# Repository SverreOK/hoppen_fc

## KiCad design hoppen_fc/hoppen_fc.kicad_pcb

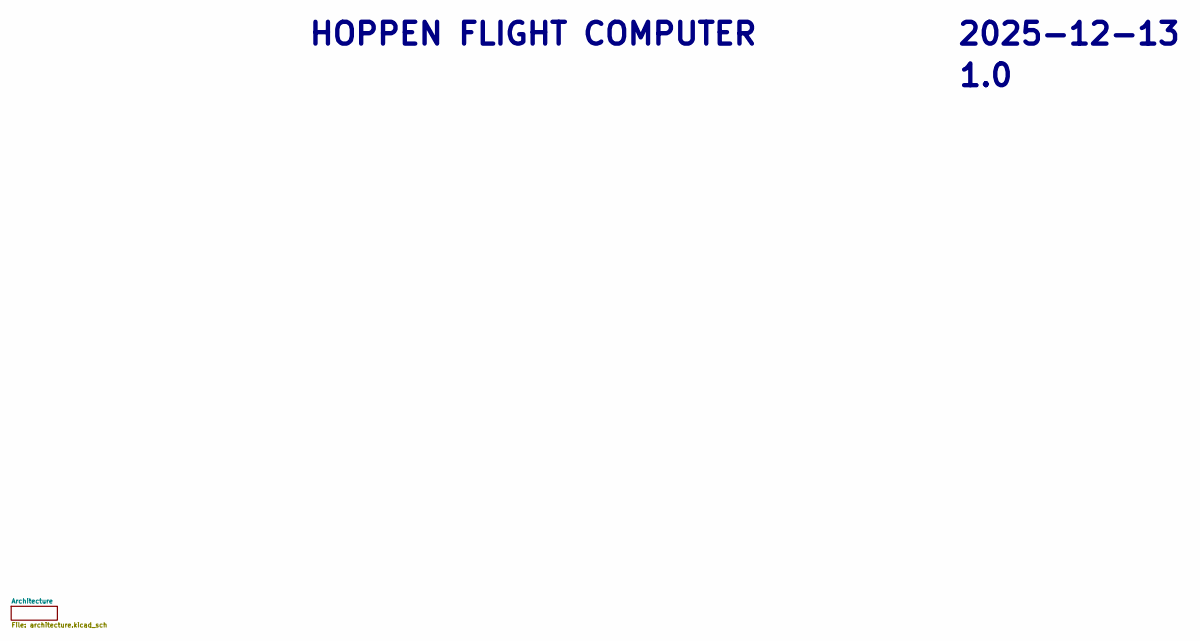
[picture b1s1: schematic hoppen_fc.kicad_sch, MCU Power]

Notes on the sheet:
${REVISION}
HOPPEN FLIGHT COMPUTER
${ISSUE_DATE}

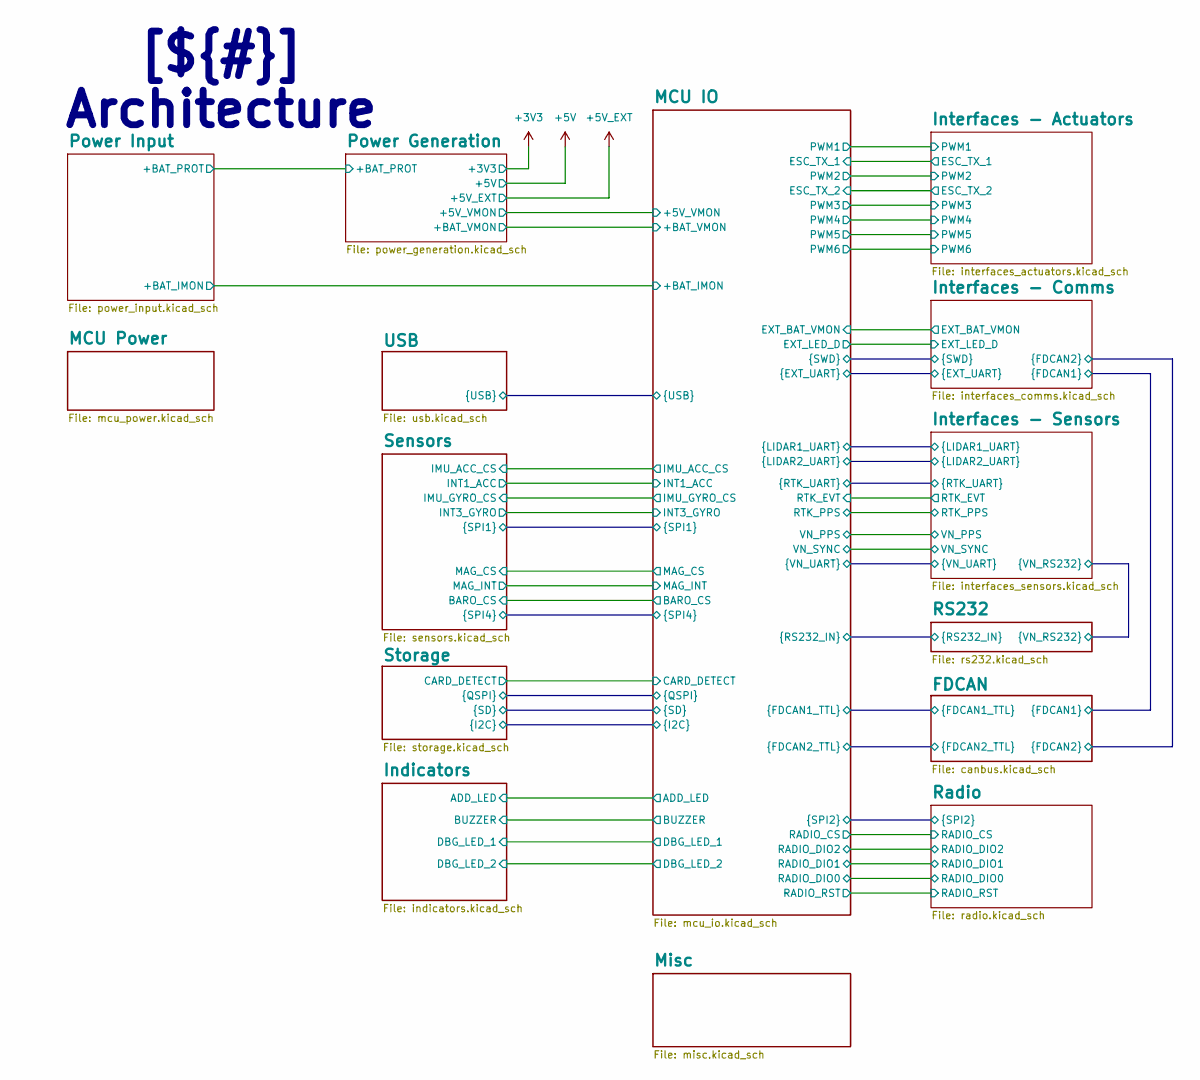
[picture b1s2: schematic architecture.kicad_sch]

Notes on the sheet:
[${#}] ${TITLE}

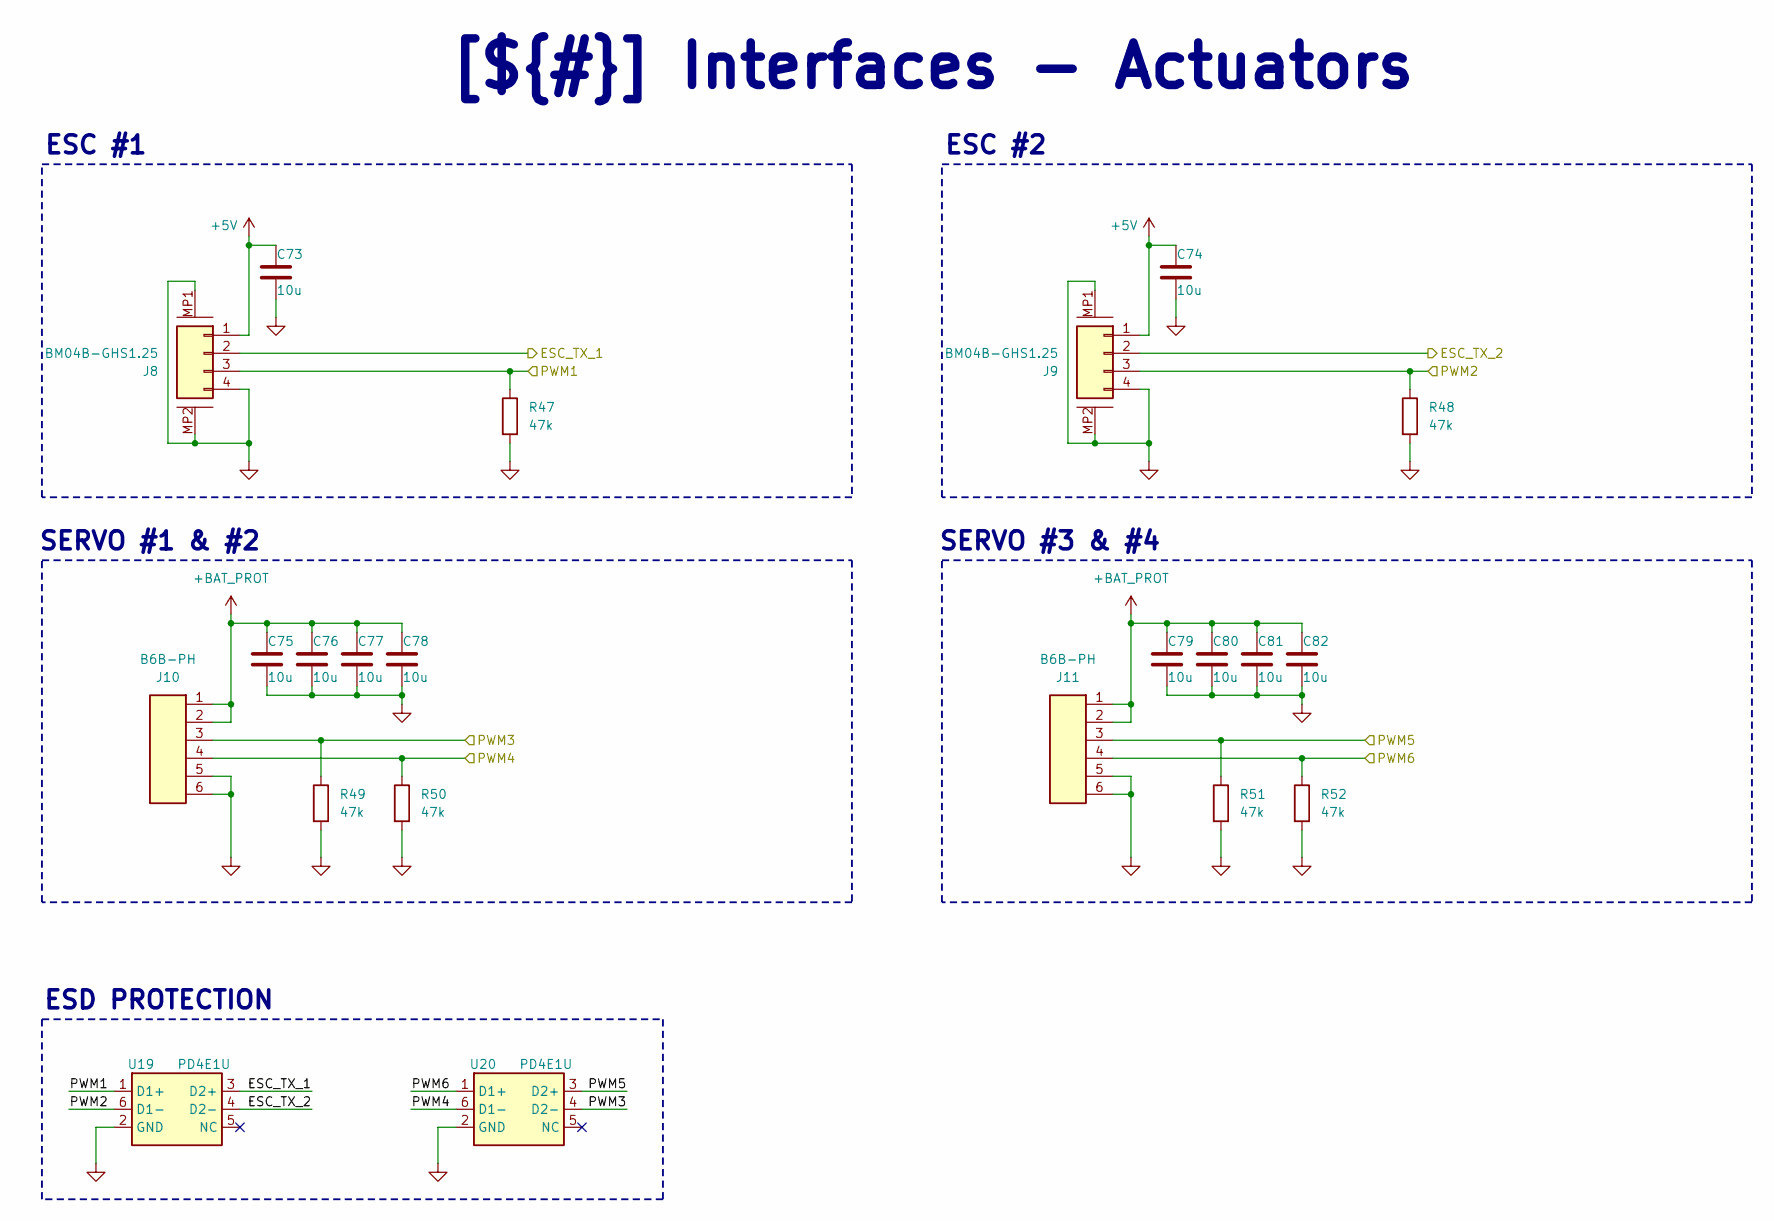
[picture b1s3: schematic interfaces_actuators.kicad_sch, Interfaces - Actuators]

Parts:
C73, C74, C75, C76, C77, C78, C79, C80, C81, C82: 10u; C_0805_2012Metric; LCSC C440198
J8, J9: BM04B-GHS1.25; LCSC C161692
J10, J11: B6B-PH; JST_PH_B6B-PH-K_1x06_P2.00mm_Vertical
R47, R48, R49, R50, R51, R52: 47k; R_0402_1005Metric; LCSC C25792
U19, U20: PD4E1U; SOT-363_SC-70-6; LCSC C194628

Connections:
+5V: C73.1, C74.1, J8.1, J9.1; also elsewhere on the board
+BAT_PROT: C75.1, C76.1, C77.1, C78.1, C79.1, C80.1, C81.1, C82.1, J10.1, J10.2, J11.1, J11.2; also elsewhere on the board
/Architecture/Interfaces - Actuators/ESC_TX_1: J8.2, U19.3 (D2+); also elsewhere on the board
/Architecture/Interfaces - Actuators/ESC_TX_2: J9.2, U19.4 (D2-); also elsewhere on the board
/Architecture/Interfaces - Actuators/PWM1: J8.3, R47.1, U19.1 (D1+); also elsewhere on the board
/Architecture/Interfaces - Actuators/PWM2: J9.3, R48.1, U19.6 (D1-); also elsewhere on the board
/Architecture/Interfaces - Actuators/PWM3: J10.3, R49.1, U20.4 (D2-); also elsewhere on the board
/Architecture/Interfaces - Actuators/PWM4: J10.4, R50.1, U20.6 (D1-); also elsewhere on the board
/Architecture/Interfaces - Actuators/PWM5: J11.3, R51.1, U20.3 (D2+); also elsewhere on the board
/Architecture/Interfaces - Actuators/PWM6: J11.4, R52.1, U20.1 (D1+); also elsewhere on the board
GND: C73.2, C74.2, C75.2, C76.2, C77.2, C78.2, C79.2, C80.2, C81.2, C82.2, J8.4, J8.MP1, J8.MP2, J9.4, J9.MP1, J9.MP2, J10.5, J10.6, J11.5, J11.6, R47.2, R48.2, R49.2, R50.2, R51.2, R52.2, U19.2 (GND), U20.2 (GND); also elsewhere on the board

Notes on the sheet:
SERVO #1 & #2
ESD PROTECTION
SERVO #3 & #4
ESC #2
ESC #1
[${#}] ${TITLE}

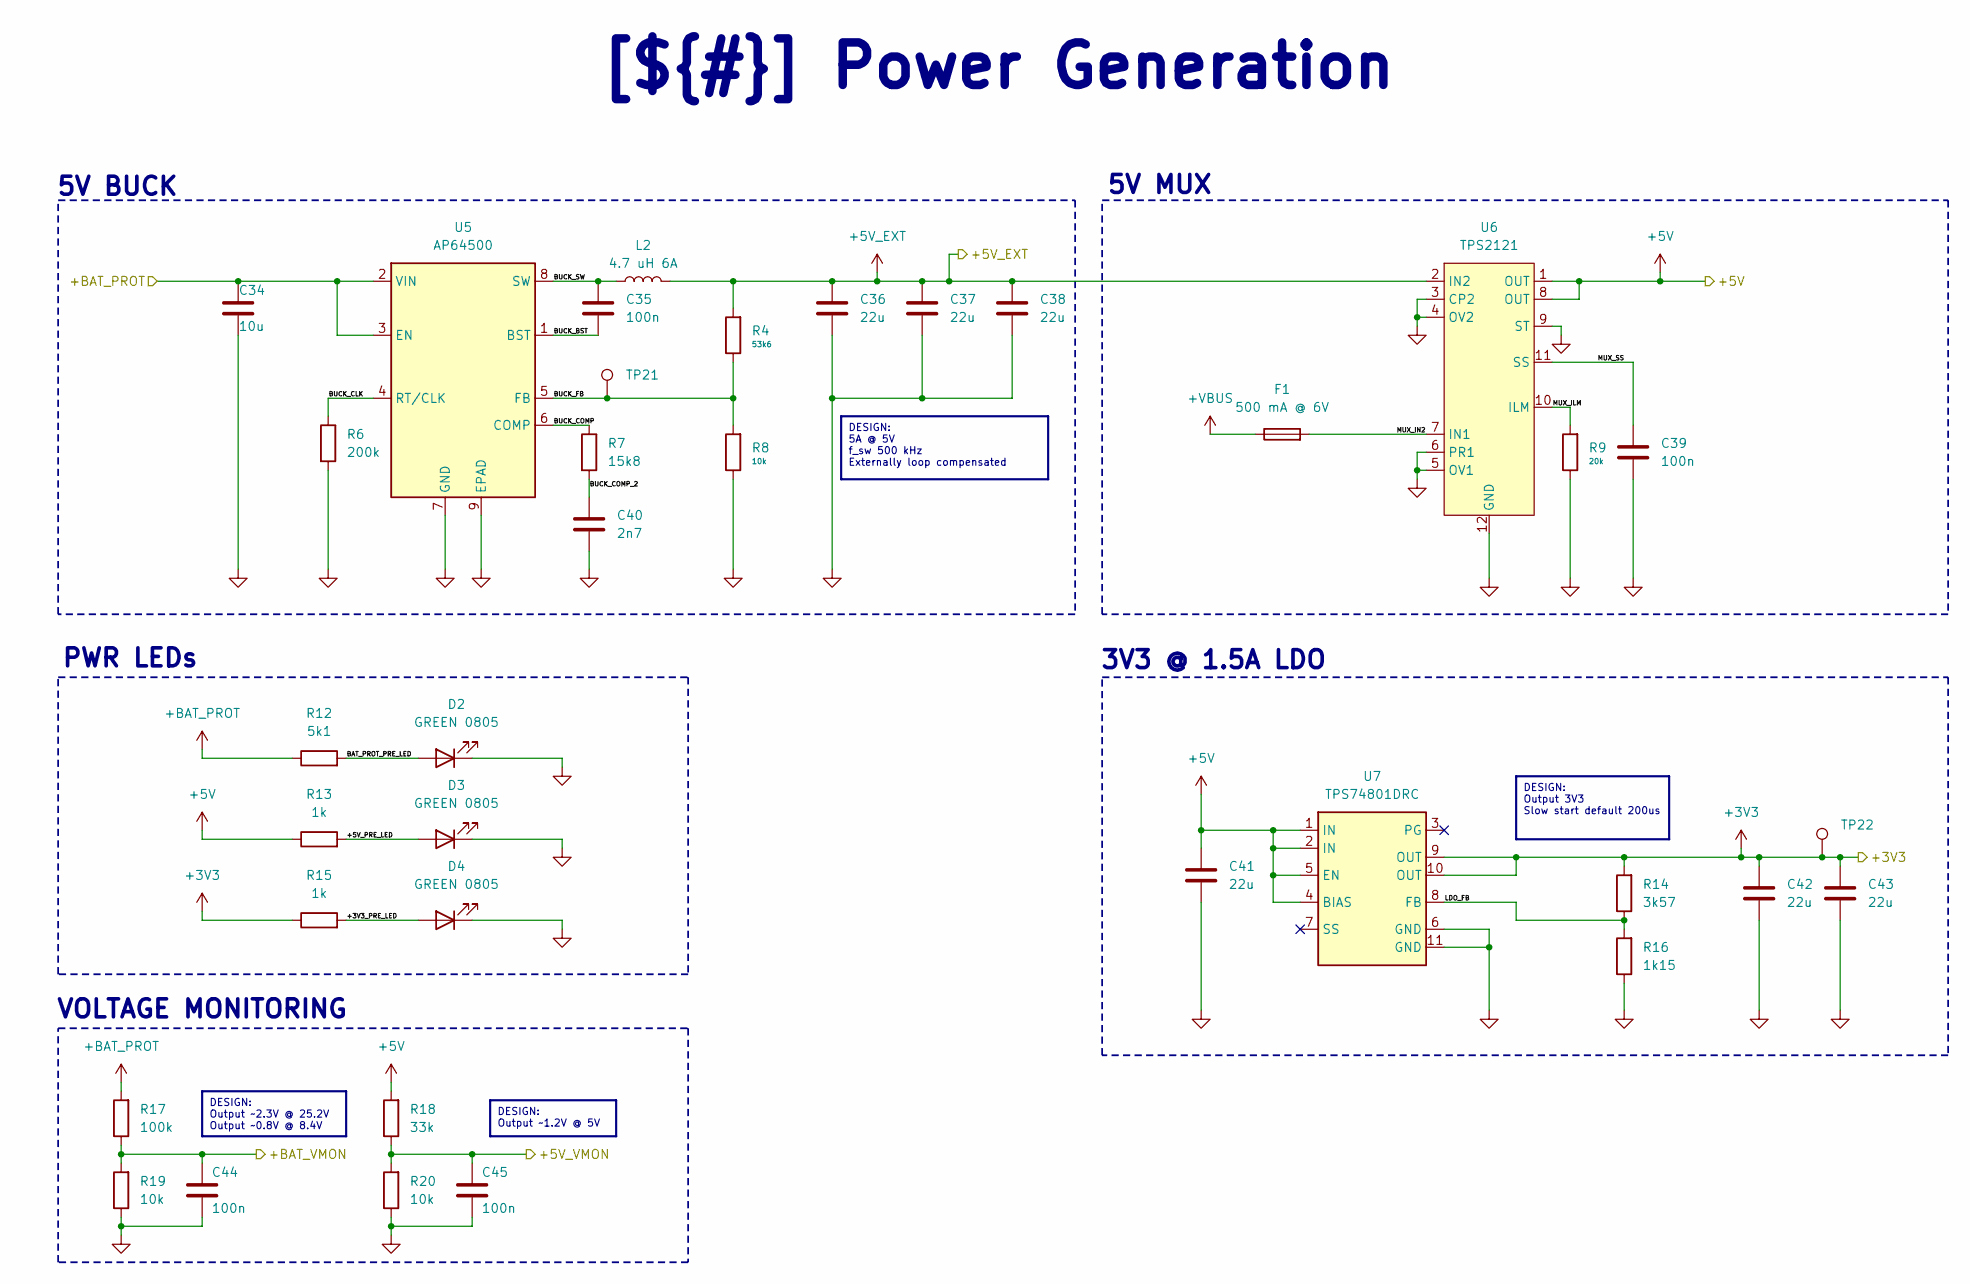
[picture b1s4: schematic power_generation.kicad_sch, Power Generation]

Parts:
C34: 10u; C_0805_2012Metric; LCSC C440198
C35, C39, C44, C45: 100n; C_0402_1005Metric; LCSC C307331
C36, C37, C38, C41, C42, C43: 22u; C_0805_2012Metric; LCSC C45783
C40: 2n7; C_0402_1005Metric; LCSC C106251
D2, D3, D4: GREEN 0805; LED_0805_2012Metric; LCSC C2297
F1: 500 mA @ 6V; Fuse_0603_1608Metric; LCSC C210357
L2: 4.7 uH 6A; IND-SMD_L7.2-W6.6_GPSR07X0; LCSC C5189754
R4: 53k6; R_0402_1005Metric; LCSC C53398
R6: 200k; R_0402_1005Metric; LCSC C25764
R7: 15k8; R_0402_1005Metric; LCSC C26956
R8, R19, R20: 10k; R_0402_1005Metric; LCSC C25744
R9: 20k; R_0402_1005Metric; LCSC C25765
R12: 5k1; R_0402_1005Metric; LCSC C25905
R13, R15: 1k; R_0402_1005Metric; LCSC C106235
R14: 3k57; R_0402_1005Metric; LCSC C270609
R16: 1k15; R_0402_1005Metric; LCSC C5159680
R17: 100k; R_0402_1005Metric; LCSC C25741
R18: 33k; R_0402_1005Metric; LCSC C25779
TP21, TP22: TestPoint; TestPoint_Pad_1.0x1.0mm
U5: AP64500; SO-8-EP; LCSC C2070920
U6: TPS2121; Texas_VQFN-HR-12_2x2.5mm_P0.5mm; LCSC C2156025
U7: TPS74801DRC; VSON-10; LCSC C105263

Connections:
+3V3: C42.1, C43.1, R14.2, R15.1, TP22.1, U7.9 (OUT), U7.10 (OUT); also elsewhere on the board
+5V: C41.1, R13.1, R18.2, U6.1 (OUT), U6.8 (OUT), U7.1 (IN), U7.2 (IN), U7.4 (BIAS), U7.5 (EN); also elsewhere on the board
+5V_EXT: C36.1, C37.1, C38.1, L2.2, R4.2, U6.2 (IN2); also elsewhere on the board
+BAT_PROT: C34.1, R12.1, R17.2, U5.2 (VIN), U5.3 (EN); also elsewhere on the board
+VBUS: F1.1; also elsewhere on the board
/Architecture/MCU IO/+5V_VMON: C45.2, R18.1, R20.2; also elsewhere on the board
/Architecture/MCU IO/+BAT_VMON: C44.2, R17.1, R19.2; also elsewhere on the board
/Architecture/Power Generation/+3V3_PRE_LED: D4.2 (A), R15.2
/Architecture/Power Generation/+5V_PRE_LED: D3.2 (A), R13.2
/Architecture/Power Generation/BAT_PROT_PRE_LED: D2.2 (A), R12.2
/Architecture/Power Generation/BUCK_BST: C35.2, U5.1 (BST)
/Architecture/Power Generation/BUCK_CLK: R6.1, U5.4 (RT/CLK)
/Architecture/Power Generation/BUCK_COMP: R7.1, U5.6 (COMP)
/Architecture/Power Generation/BUCK_COMP_2: C40.1, R7.2
/Architecture/Power Generation/BUCK_FB: R4.1, R8.2, TP21.1, U5.5 (FB)
/Architecture/Power Generation/BUCK_SW: C35.1, L2.1, U5.8 (SW)
/Architecture/Power Generation/LDO_FB: R14.1, R16.2, U7.8 (FB)
/Architecture/Power Generation/MUX_ILM: R9.2, U6.10 (ILM)
/Architecture/Power Generation/MUX_IN2: F1.2, U6.7 (IN1)
/Architecture/Power Generation/MUX_SS: C39.1, U6.11 (SS)
GND: C34.2, C36.2, C37.2, C38.2, C39.2, C40.2, C41.2, C42.2, C43.2, C44.1, C45.1, D2.1 (K), D3.1 (K), D4.1 (K), R6.2, R8.1, R9.1, R16.1, R19.1, R20.1, U5.7 (GND), U5.9 (EPAD), U6.3 (CP2), U6.4 (OV2), U6.5 (OV1), U6.6 (PR1), U6.9 (ST), U6.12 (GND), U7.6 (GND), U7.11 (GND); also elsewhere on the board

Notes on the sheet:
5V MUX
PWR LEDs
5V BUCK
VOLTAGE MONITORING
3V3 @ 1.5A LDO
[${#}] ${TITLE}
DESIGN: Output 3V3 Slow start default 200us
DESIGN: 5A @ 5V f_sw 500 kHz Externally loop compensated
DESIGN: Output ~1.2V @ 5V
DESIGN: Output ~2.3V @ 25.2V Output ~0.8V @ 8.4V

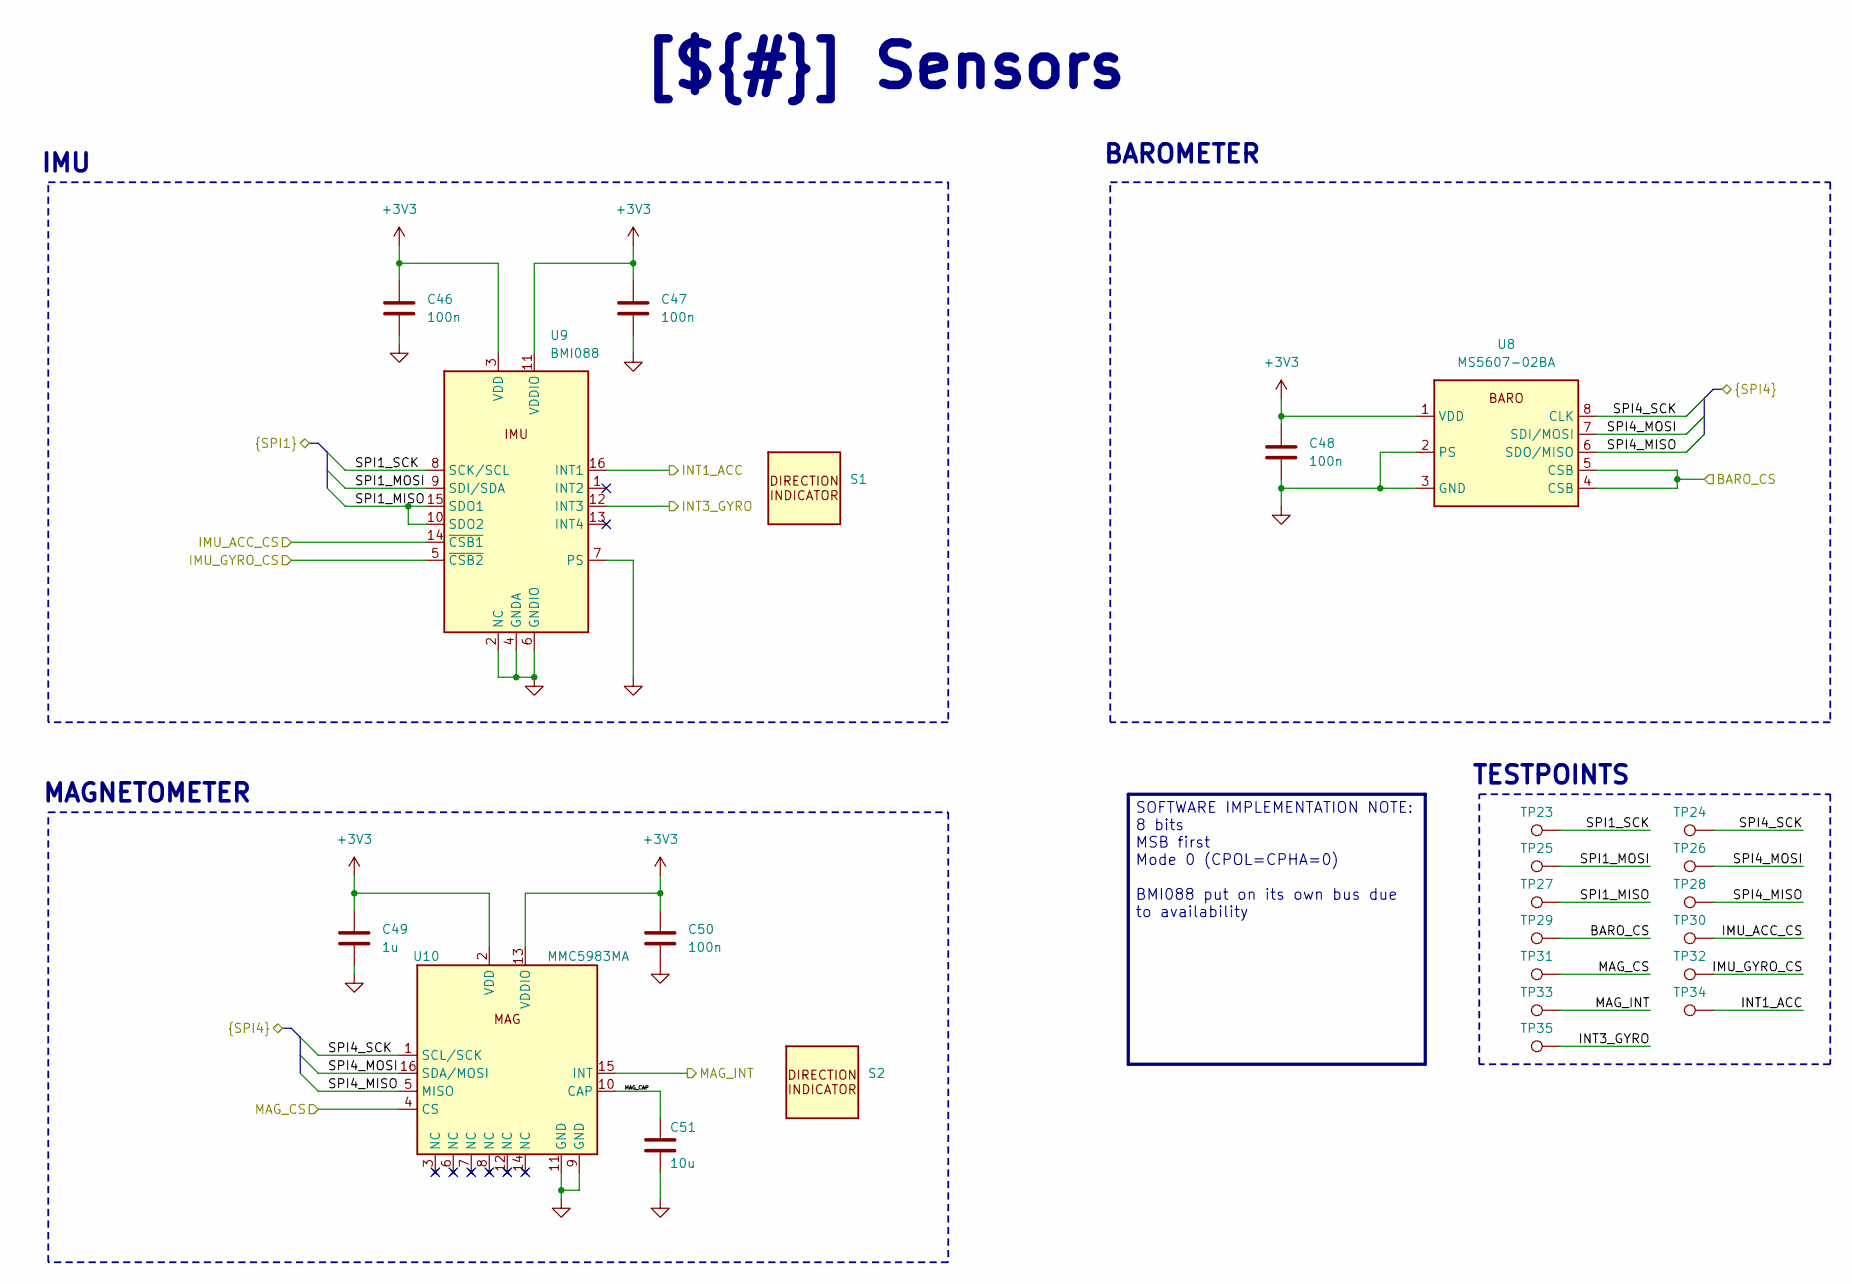
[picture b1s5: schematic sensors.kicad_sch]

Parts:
C46, C47, C48, C50: 100n; C_0402_1005Metric; LCSC C307331
C49: 1u; C_0402_1005Metric; LCSC C52923
C51: 10u; C_0805_2012Metric; LCSC C440198
S1: right_hand_rule
S2: right_hand_rule_2
TP23, TP24, TP25, TP26, TP27, TP28, TP29, TP30, TP31, TP32, TP33, TP34, TP35: TestPoint; TestPoint_Pad_1.0x1.0mm
U8: MS5607-02BA; LGA-8_3x5mm_P1.25mm; LCSC C97627
U9: BMI088; Bosch_LGA-16_4.5x3mm_P0.5mm_LayoutBorder7x1y_ClockwisePinNu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; LCSC C194919
U10: MMC5983MA; LGA-16_3x3mm_P0.5mm; LCSC C404329

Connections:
+3V3: C46.1, C47.1, C48.1, C49.1, C50.1, U8.1 (VDD), U9.3 (VDD), U9.11 (VDDIO), U10.2 (VDD), U10.13 (VDDIO); also elsewhere on the board
/Architecture/MCU IO/BARO_CS: TP29.1, U8.4 (CSB), U8.5 (CSB); also elsewhere on the board
/Architecture/MCU IO/IMU_ACC_CS: TP30.1, U9.14 (~CSB1); also elsewhere on the board
/Architecture/MCU IO/IMU_GYRO_CS: TP32.1, U9.5 (~CSB2); also elsewhere on the board
/Architecture/MCU IO/INT1_ACC: TP34.1, U9.16 (INT1); also elsewhere on the board
/Architecture/MCU IO/INT3_GYRO: TP35.1, U9.12 (INT3); also elsewhere on the board
/Architecture/MCU IO/MAG_CS: TP31.1, U10.4 (CS); also elsewhere on the board
/Architecture/MCU IO/MAG_INT: TP33.1, U10.15 (INT); also elsewhere on the board
/Architecture/MCU IO/SPI1_MISO: TP27.1, U9.10 (SDO2), U9.15 (SDO1); also elsewhere on the board
/Architecture/MCU IO/SPI1_MOSI: TP25.1, U9.9 (SDI/SDA); also elsewhere on the board
/Architecture/MCU IO/SPI1_SCK: TP23.1, U9.8 (SCK/SCL); also elsewhere on the board
/Architecture/MCU IO/SPI4_MISO: TP28.1, U8.6 (SDO/MISO), U10.5 (MISO); also elsewhere on the board
/Architecture/MCU IO/SPI4_MOSI: TP26.1, U8.7 (SDI/MOSI), U10.16 (SDA/MOSI); also elsewhere on the board
/Architecture/MCU IO/SPI4_SCK: TP24.1, U8.8 (CLK), U10.1 (SCL/SCK); also elsewhere on the board
/Architecture/Sensors/MAG_CAP: C51.2, U10.10 (CAP)
GND: C46.2, C47.2, C48.2, C49.2, C50.2, C51.1, U8.2 (PS), U8.3 (GND), U9.2 (NC), U9.4 (GNDA), U9.6 (GNDIO), U9.7 (PS), U10.9 (GND), U10.11 (GND); also elsewhere on the board

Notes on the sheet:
BAROMETER
MAGNETOMETER
TESTPOINTS
IMU
[${#}] ${TITLE}
SOFTWARE IMPLEMENTATION NOTE: 8 bits MSB first Mode 0 (CPOL=CPHA=0) BMI088 put on its own bus due to availability

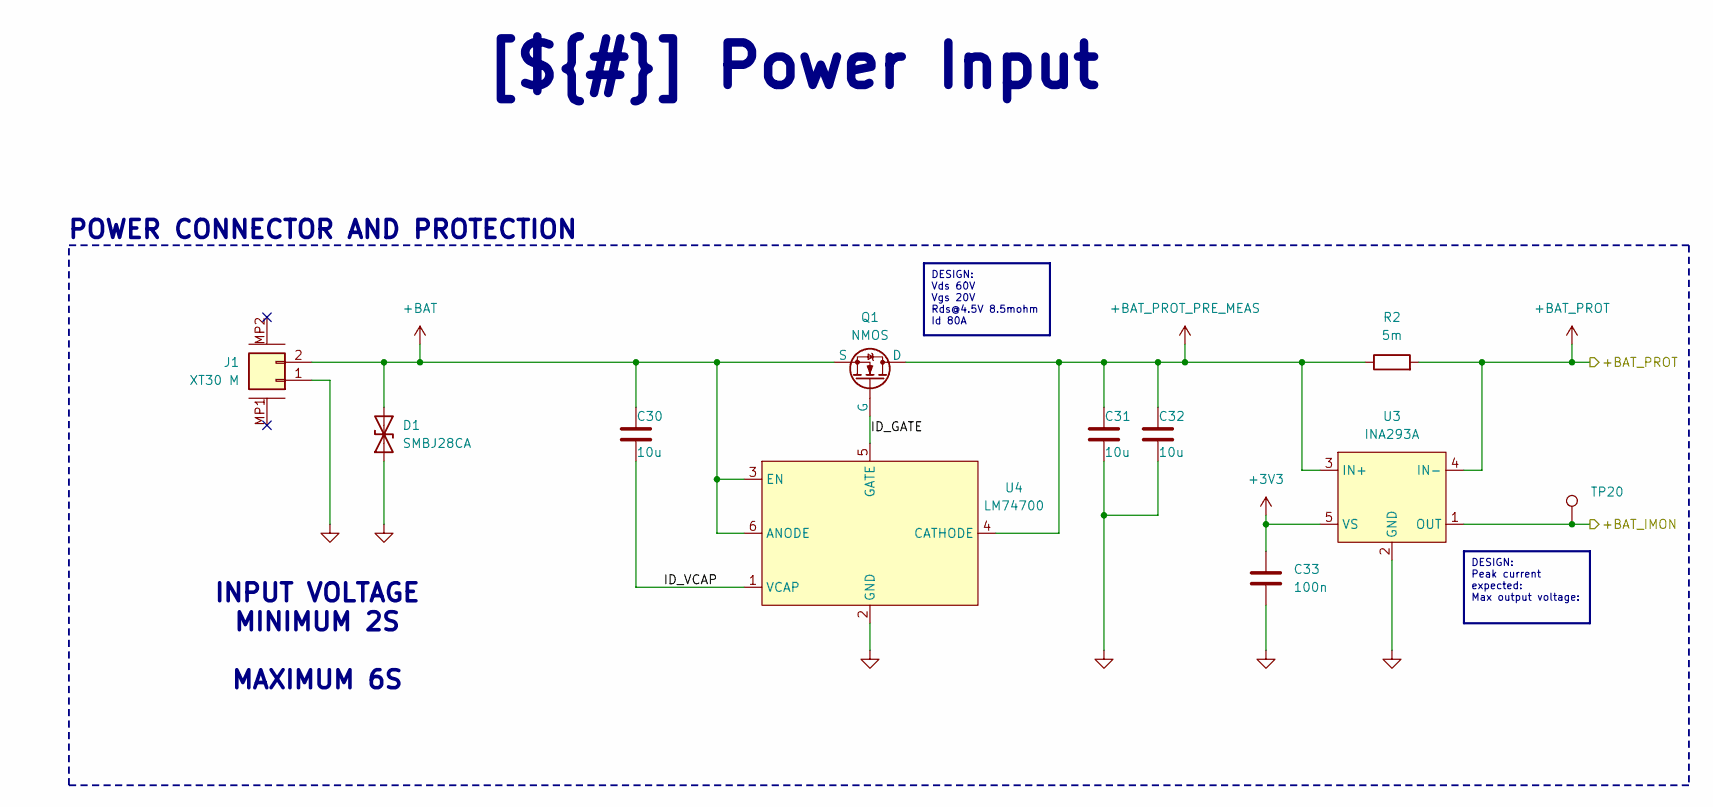
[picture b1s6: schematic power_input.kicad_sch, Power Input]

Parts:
C30, C31, C32: 10u; C_0805_2012Metric; LCSC C440198
C33: 100n; C_0402_1005Metric; LCSC C307331
D1: SMBJ28CA; D_SMB; LCSC C19077583
J1: XT30 M; XT30PW-M
Q1: NMOS; Diodes_PowerDI3333-8; LCSC C2802568
R2: 5m; R_2512_6332Metric; LCSC C185817
TP20: TestPoint; TestPoint_Pad_1.0x1.0mm
U3: INA293A; SOT-23-5; LCSC C1855790
U4: LM74700; SOT-23-6; LCSC C2941042

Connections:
+3V3: C33.1, U3.5 (VS); also elsewhere on the board
+BAT: C30.1, D1.2 (A2), J1.2, Q1.3 (S), U4.3 (EN), U4.6 (ANODE)
+BAT_PROT: R2.2, U3.4 (IN-); also elsewhere on the board
+BAT_PROT_PRE_MEAS: C31.1, C32.1, Q1.1 (D), R2.1, U3.3 (IN+), U4.4 (CATHODE)
/Architecture/MCU IO/+BAT_IMON: TP20.1, U3.1 (OUT); also elsewhere on the board
/Architecture/Power Input/ID_GATE: Q1.2 (G), U4.5 (GATE)
/Architecture/Power Input/ID_VCAP: C30.2, U4.1 (VCAP)
GND: C31.2, C32.2, C33.2, D1.1 (A1), J1.1, U3.2 (GND), U4.2 (GND); also elsewhere on the board

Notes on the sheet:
POWER CONNECTOR AND PROTECTION
INPUT VOLTAGE MINIMUM 2S MAXIMUM 6S
DESIGN: Peak current expected: Max output voltage:
[${#}] ${TITLE}
DESIGN: Vds 60V Vgs 20V Rds@4.5V 8.5mohm Id 80A

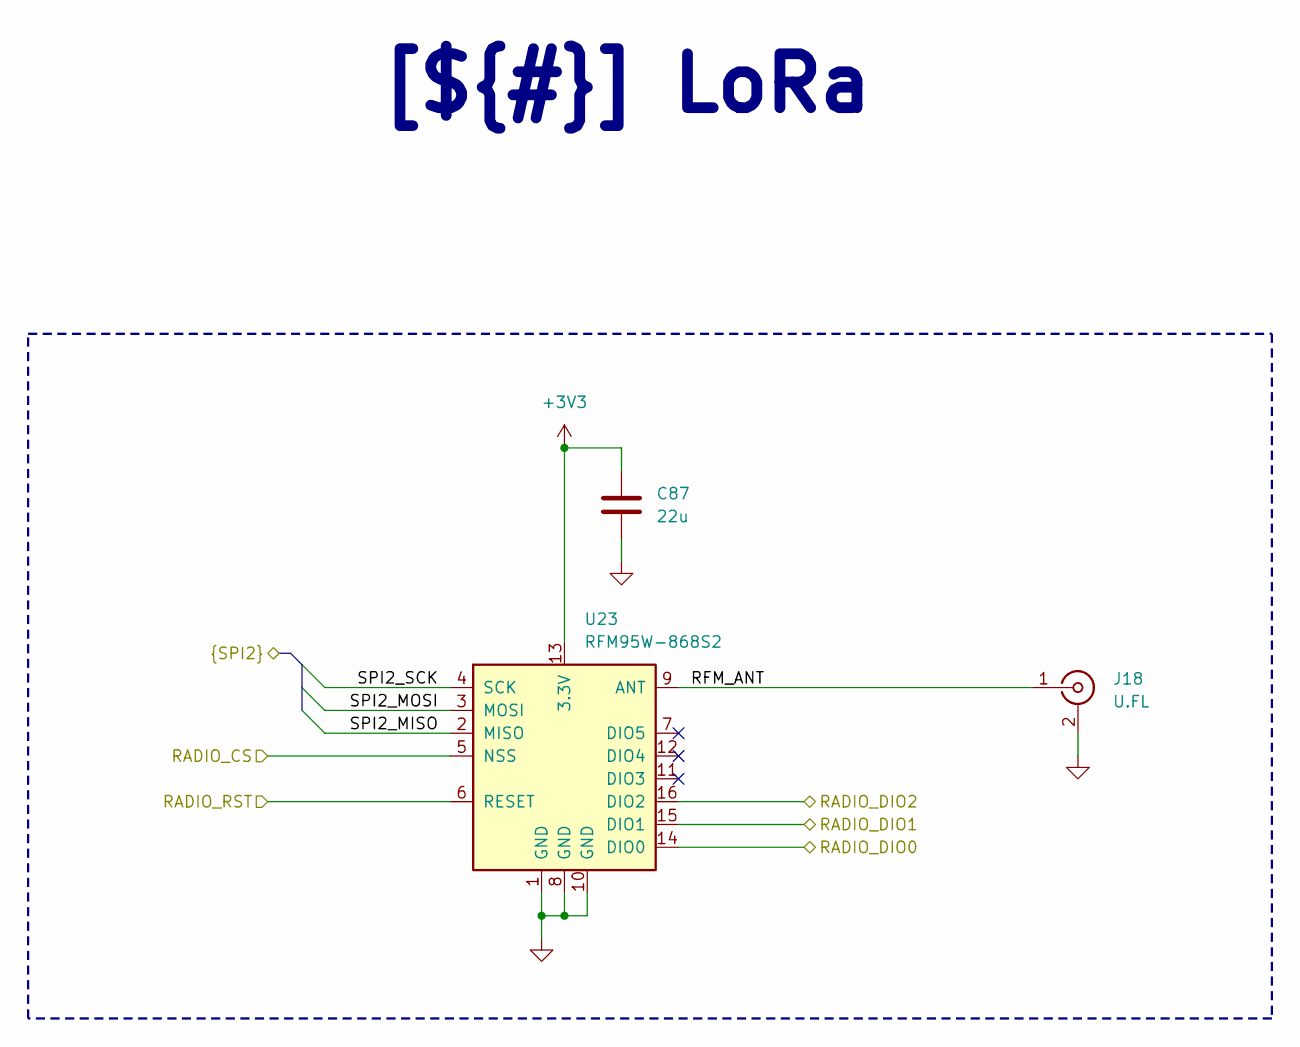
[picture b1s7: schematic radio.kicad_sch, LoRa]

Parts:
C87: 22u; C_0805_2012Metric; LCSC C45783
J18: U.FL; U.FL_Hirose_U.FL-R-SMT-1_Vertical; LCSC C88374
U23: RFM95W-868S2; HOPERF_RFM9XW_SMD

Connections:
+3V3: C87.1, U23.13 (3.3V); also elsewhere on the board
/Architecture/MCU IO/RADIO_CS: U23.5 (NSS); also elsewhere on the board
/Architecture/MCU IO/RADIO_DIO0: U23.14 (DIO0); also elsewhere on the board
/Architecture/MCU IO/RADIO_DIO1: U23.15 (DIO1); also elsewhere on the board
/Architecture/MCU IO/RADIO_DIO2: U23.16 (DIO2); also elsewhere on the board
/Architecture/MCU IO/RADIO_RST: U23.6 (RESET); also elsewhere on the board
/Architecture/MCU IO/SPI2_MISO: U23.2 (MISO); also elsewhere on the board
/Architecture/MCU IO/SPI2_MOSI: U23.3 (MOSI); also elsewhere on the board
/Architecture/MCU IO/SPI2_SCK: U23.4 (SCK); also elsewhere on the board
/Architecture/Radio/RFM_ANT: J18.1 (In), U23.9 (ANT)
GND: C87.2, J18.2 (Ext), U23.1 (GND), U23.8 (GND), U23.10 (GND); also elsewhere on the board

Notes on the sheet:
[${#}] ${TITLE}

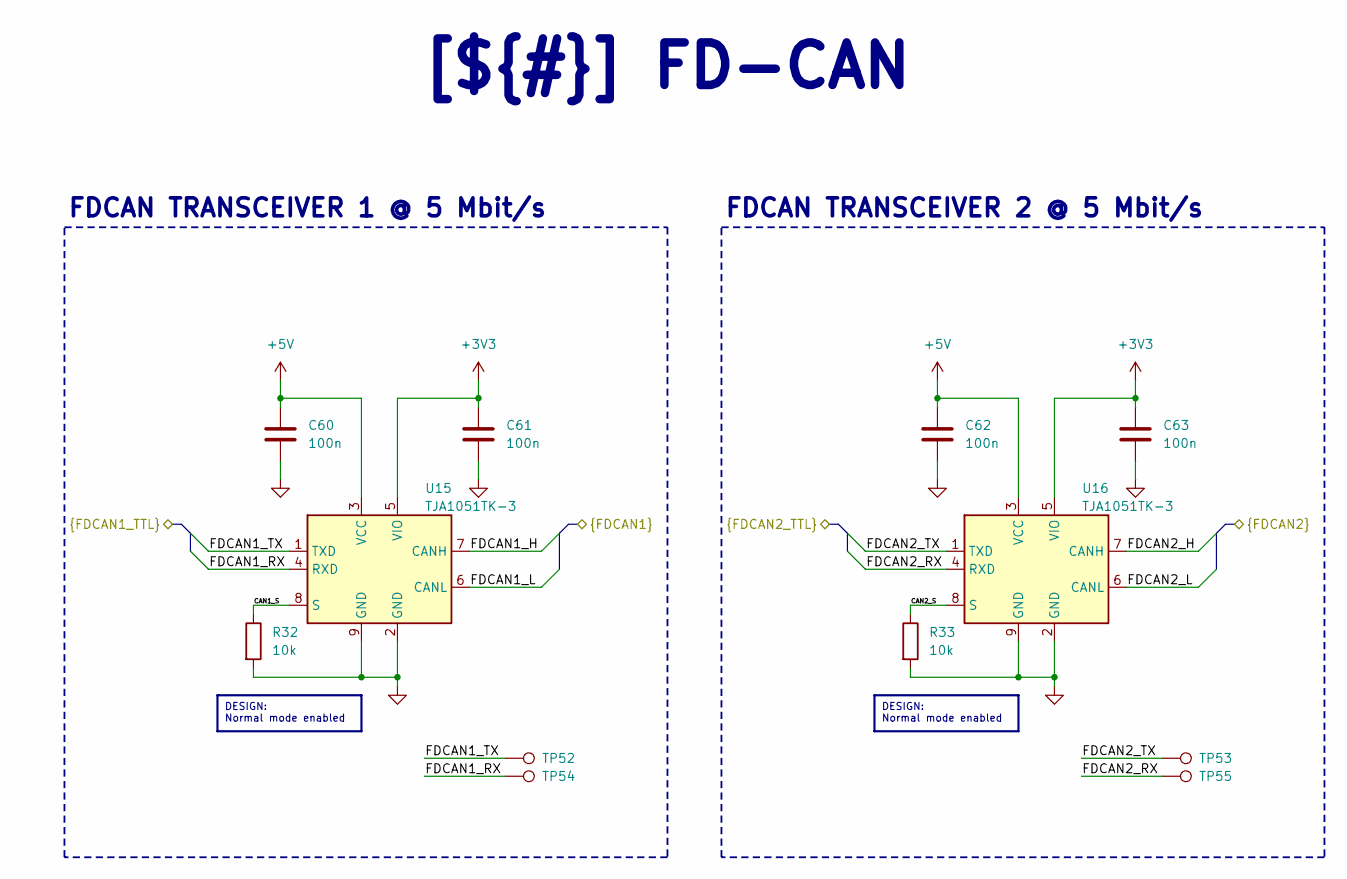
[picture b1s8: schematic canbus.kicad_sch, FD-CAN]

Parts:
C60, C61, C62, C63: 100n; C_0402_1005Metric; LCSC C307331
R32, R33: 10k; R_0402_1005Metric; LCSC C25744
TP52, TP53, TP54, TP55: TestPoint; TestPoint_Pad_1.0x1.0mm
U15, U16: TJA1051TK-3; HVSON-8-1EP_3x3mm_P0.65mm_EP1.6x2.4mm; LCSC C2875699

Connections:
+3V3: C61.1, C63.1, U15.5 (VIO), U16.5 (VIO); also elsewhere on the board
+5V: C60.1, C62.1, U15.3 (VCC), U16.3 (VCC); also elsewhere on the board
/Architecture/FDCAN/CAN1_S: R32.1, U15.8 (S)
/Architecture/FDCAN/CAN2_S: R33.1, U16.8 (S)
/Architecture/FDCAN/FDCAN1_H: U15.7 (CANH); also elsewhere on the board
/Architecture/FDCAN/FDCAN1_L: U15.6 (CANL); also elsewhere on the board
/Architecture/FDCAN/FDCAN1_RX: TP54.1, U15.4 (RXD); also elsewhere on the board
/Architecture/FDCAN/FDCAN1_TX: TP52.1, U15.1 (TXD); also elsewhere on the board
/Architecture/FDCAN/FDCAN2_H: U16.7 (CANH); also elsewhere on the board
/Architecture/FDCAN/FDCAN2_L: U16.6 (CANL); also elsewhere on the board
/Architecture/FDCAN/FDCAN2_RX: TP55.1, U16.4 (RXD); also elsewhere on the board
/Architecture/FDCAN/FDCAN2_TX: TP53.1, U16.1 (TXD); also elsewhere on the board
GND: C60.2, C61.2, C62.2, C63.2, R32.2, R33.2, U15.2 (GND), U15.9 (GND), U16.2 (GND), U16.9 (GND); also elsewhere on the board

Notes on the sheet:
FDCAN TRANSCEIVER 1 @ 5 Mbit/s
FDCAN TRANSCEIVER 2 @ 5 Mbit/s
[${#}] ${TITLE}
DESIGN: Normal mode enabled

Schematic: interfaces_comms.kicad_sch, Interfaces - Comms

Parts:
C83, C84, C86: 22u; C_0805_2012Metric; LCSC C45783
C85: 100n; C_0402_1005Metric; LCSC C307331
D13: SMF28CA; D_SOD-123FL; Part SMF28CA; LCSC C19077517
J12, J13, J17: BM04B-GHS1.25; LCSC C161692
J14, J16: BM02B-GHS1.25; LCSC C225118
J15: BM05B-GHS1.25; LCSC C225121
JP3, JP4: J; SolderJumper-2_P1.3mm_Bridged_RoundedPad1.0x1.5mm
JP5: SolderJumper_3_Open; SolderJumper-3_P1.3mm_Open_Pad1.0x1.5mm
R53, R54: 120R; R_0402_1005Metric; LCSC C25079
R55: 100k; R_0402_1005Metric; LCSC C25741
R56: 10k; R_0402_1005Metric; LCSC C25744
R57, R58: 22R; R_0402_1005Metric; LCSC C2929994
U21: 74AHCT1G125; SOT-23-5; LCSC C20617903
U22: PD4E1U; SOT-363_SC-70-6; LCSC C194628

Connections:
+3V3: J15.1, JP5.3 (B); also elsewhere on the board
+5V: C83.1, C84.1, J12.1, J13.1, JP5.1 (A), U21.5 (VCC); also elsewhere on the board
/Architecture/FDCAN/FDCAN1_H: J12.2, JP3.2 (B); also elsewhere on the board
/Architecture/FDCAN/FDCAN1_L: J12.3, R53.1; also elsewhere on the board
/Architecture/FDCAN/FDCAN2_H: J13.2, JP4.2 (B); also elsewhere on the board
/Architecture/FDCAN/FDCAN2_L: J13.3, R54.1; also elsewhere on the board
/Architecture/Interfaces - Comms/EXT_BAT: D13.2, J14.1, R55.1
/Architecture/Interfaces - Comms/EXT_LED_D_5V: J16.1, U21.4
/Architecture/Interfaces - Comms/EXT_UART_PWR: C86.1, J17.1, JP5.2 (C)
/Architecture/Interfaces - Comms/EXT_UART_RX: R58.2; also elsewhere on the board
/Architecture/Interfaces - Comms/EXT_UART_RX_T: J17.3, R58.1
/Architecture/Interfaces - Comms/EXT_UART_TX: R57.2; also elsewhere on the board
/Architecture/Interfaces - Comms/EXT_UART_TX_T: J17.2, R57.1
/Architecture/Interfaces - Comms/FDCAN_T_1_J: JP3.1 (A), R53.2
/Architecture/Interfaces - Comms/FDCAN_T_2_J: JP4.1 (A), R54.2
/Architecture/Interfaces - Comms/NRST: J15.4; also elsewhere on the board
/Architecture/Interfaces - Comms/SWCLK: J15.3, U22.6 (D1-); also elsewhere on the board
/Architecture/Interfaces - Comms/SWDIO: J15.2, U22.1 (D1+); also elsewhere on the board
/Architecture/MCU IO/EXT_BAT_VMON: C85.1, R55.2, R56.1; also elsewhere on the board
/Architecture/MCU IO/EXT_LED_D: U21.2; also elsewhere on the board
GND: C83.2, C84.2, C85.2, C86.2, D13.1, J12.4, J12.MP1, J12.MP2, J13.4, J13.MP1, J13.MP2, J14.2, J14.MP1, J14.MP2, J15.5, J15.MP1, J15.MP2, J16.2, J16.MP1, J16.MP2, J17.4, J17.MP1, J17.MP2, R56.2, U21.1, U21.3 (GND), U22.2 (GND); also elsewhere on the board

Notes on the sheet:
FDCAN #1
SERIAL WIRE DEBUG
BATTERY VMON INPUT
MAX 6S
ESD PROTECTION
EXTERNAL UART
FDCAN #2
LED STRIP
[${#}] ${TITLE}
DESIGN: Possibly change to 6P due to availability
DESIGN: ESD included in FDCAN transceiver
DESIGN: 4S (16.8V) to ~1.5 V 3S (12.6V) to ~1.1 V

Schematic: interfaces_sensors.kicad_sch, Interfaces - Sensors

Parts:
C69, C70, C71, C72: 22u; C_0805_2012Metric; LCSC C45783
J4, J5: BM04B-GHS1.25; LCSC C161692
J6: BM06B-GHS1.25; BM06B-GHS-1.25; LCSC C225122
J7: BM08B-GHS1.25; LCSC C133062
R39, R40, R41, R42, R43, R44, R45, R46: 22R; R_0402_1005Metric; LCSC C2929994
U18: PD4E1U; SOT-363_SC-70-6; LCSC C194628

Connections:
+5V: C69.1, C70.1, C71.1, C72.1, J4.1, J5.1, J6.1, J7.1; also elsewhere on the board
/Architecture/Interfaces - Sensors/LIDAR1_T_UART_RX: J4.3, R41.1
/Architecture/Interfaces - Sensors/LIDAR1_T_UART_TX: J4.2, R39.1
/Architecture/Interfaces - Sensors/LIDAR1_UART_RX: R41.2; also elsewhere on the board
/Architecture/Interfaces - Sensors/LIDAR1_UART_TX: R39.2; also elsewhere on the board
/Architecture/Interfaces - Sensors/LIDAR2_T_UART_RX: J5.3, R42.1
/Architecture/Interfaces - Sensors/LIDAR2_T_UART_TX: J5.2, R40.1
/Architecture/Interfaces - Sensors/LIDAR2_UART_RX: R42.2; also elsewhere on the board
/Architecture/Interfaces - Sensors/LIDAR2_UART_TX: R40.2; also elsewhere on the board
/Architecture/Interfaces - Sensors/RTK_UART_RX: R44.2; also elsewhere on the board
/Architecture/Interfaces - Sensors/RTK_UART_RX_T: J6.3, R44.1
/Architecture/Interfaces - Sensors/RTK_UART_TX: R43.2; also elsewhere on the board
/Architecture/Interfaces - Sensors/RTK_UART_TX_T: J6.2, R43.1
/Architecture/Interfaces - Sensors/VN_RS232_RX: J7.3; also elsewhere on the board
/Architecture/Interfaces - Sensors/VN_RS232_TX: J7.2; also elsewhere on the board
/Architecture/Interfaces - Sensors/VN_UART_RX: R46.2; also elsewhere on the board
/Architecture/Interfaces - Sensors/VN_UART_RX_T: J7.7, R46.1, U18.3 (D2+)
/Architecture/Interfaces - Sensors/VN_UART_TX: R45.2; also elsewhere on the board
/Architecture/Interfaces - Sensors/VN_UART_TX_T: J7.6, R45.1, U18.4 (D2-)
/Architecture/MCU IO/RTK_EVT: J6.5; also elsewhere on the board
/Architecture/MCU IO/RTK_PPS: J6.4; also elsewhere on the board
/Architecture/MCU IO/VN_PPS: J7.4, U18.1 (D1+); also elsewhere on the board
/Architecture/MCU IO/VN_SYNC: J7.5, U18.6 (D1-); also elsewhere on the board
GND: C69.2, C70.2, C71.2, C72.2, J4.4, J4.MP1, J4.MP2, J5.4, J5.MP1, J5.MP2, J6.6, J6.MP1, J6.MP2, J7.8, J7.MP1, J7.MP2, U18.2 (GND); also elsewhere on the board

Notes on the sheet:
VN300 INTEREFACE
ZED X20P INTERFACE
LIDAR INTERFACE #2
LIDAR INTERFACE #1
DESIGN: Series resistors included due to distance
DESIGN: ESD included in RS233 transceiver
SOFTWARE IMPLEMENTATION NOTE: Two UART implemented due to RTK feedback. See VN300 ext. GNSS note.
[${#}] ${TITLE}

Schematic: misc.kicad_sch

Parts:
FID1, FID2, FID3, FID4, FID5, FID6: Fiducial; Fiducial_1mm_Mask2mm
H1, H2, H3, H4: M3; MountingHole_3.2mm_M3_Pad_Via

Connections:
GND: H1.MP, H2.MP, H3.MP, H4.MP; also elsewhere on the board

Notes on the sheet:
FIDUCIALS (FRONT & BACK)
M3 MOUNTING HOLES
[${#}] ${TITLE}

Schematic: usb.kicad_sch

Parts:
D5: SMF5V0A; D_SMF; LCSC C1972946
J2: USB_C_Receptacle_USB2.0_16P; USB-C_SMD-TYPE-C-31-M-12_1; LCSC C165948
R21, R22: 22R; R_0402_1005Metric; LCSC C2929994
R23, R24: 5k1; R_0402_1005Metric; LCSC C25905
U11: USBLC6-2SC6; SOT-23-6; LCSC C7519

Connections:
+VBUS: D5.1 (A1), J2.A4B9 (VBUS), J2.B4A9 (VBUS), U11.5 (VBUS); also elsewhere on the board
/Architecture/MCU IO/USB_N: R21.1; also elsewhere on the board
/Architecture/MCU IO/USB_P: R22.2; also elsewhere on the board
/Architecture/USB/CC1: J2.A5 (CC1), R24.1
/Architecture/USB/CC2: J2.B5 (CC2), R23.1
/Architecture/USB/USB_NT_N: J2.A7 (D-), J2.B7 (D-), R21.2, U11.1 (I/O1), U11.6 (I/O1)
/Architecture/USB/USB_NT_P: J2.A6 (D+), J2.B6 (D+), R22.1, U11.3 (I/O2), U11.4 (I/O2)
GND: D5.2 (A2), J2.A1B12 (GND), J2.B1A12 (GND), R23.2, R24.2, U11.2 (GND); also elsewhere on the board

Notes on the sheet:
[${#}] ${TITLE}
